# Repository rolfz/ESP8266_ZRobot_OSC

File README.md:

# ESP8266_ZRobot_OSC

EPS8266 based Robot with OSC based remote control. Robot can be controlled by iPhone or Smartphone, both config files are included.
The robot was based on FTobler Thingiverse 3d design http://www.thingiverse.com/thing:1230244

Functionality: The robot code was basically made to test the TOUCHOSC interface. OSC allows to communicate both 
	ways between ESP8266 and a smart-phone. All code runs on the ESP module (No Arduino Hardware required).
- "Speed" cursor will define the speed of the step motors advance.
- "Direction" cursor adds or deducts a value from the speed making the robot turn left-right
- "Reverse" button inverses the motor rotation = reverse the engine direction like a car.
- 3 buttons "Turn Left, Center, Turn right" are preprogrammed directions for the robot
- "RUN" button will start the engine and also stop everything if cancelled.
- One status line is used to send instructions to the pilot
- One distance message box will indicate the distance to the next object (to be implemented).
- Current time and Smartphone battery are shown on the display

### Basic ideas, origin of the project:

- ftobler 3d files printed on Lulzbot TAZ4 printer.
- two 28byj-48 stepper motors with driver circuit from ebay
- ESP8266 12E module
	
###Changes, additions:

- ESP was programmed with Arduino based environment and ESP plug-in
- Accelstepper library (http://www.airspayce.com/mikem/arduino/AccelStepper/).
- Tutorial can be found here: (https://www.pjrc.com/teensy/td_libs_AccelStepper.html).
- LV-MAXSonar-EZ0 from Sparkfun
- self made board to hold the ESP module, with 2 push buttons for reset and setting programming mode, 
  led and connectors for the peripherals.
- Alternative battery holder to hold a 2S Lipo
- Alternative motor connections to simplify the wiring on the self made board.

### TouchOSC:

I discovered this app by accident when I looked at B-Robot and similar projects. Some tests made with 
Blynk which looks even more attractive made visible the current advantage of OSC! Easy implementation,
easy to use windows application to create the GUI, easy to load on a second or alternative platform 
and sizable widgets which are not yet possible on Blynk made me keep OSC for this project. Maybe I 
missed something on Blynk, at least it was not immediately visible that the features I missed where 
available. TouchOSC design tool is available for free from http://hexler.net/software/touchosc, you 
will need to pay for the user interface you download on your phone or tablet.

My current TouchOSC design:

OSC config: 
----------
Simple-Z-Robot-Iphone5.touchosc
Simple-Z-Robot-Samsung.touchosc
	
Code:
----
ESP8266_ZRobot_OSC.ino includes all Zrobot specific code.

Schematic:
---------
[schematic.pdf](schematic.pdf) and eagle files

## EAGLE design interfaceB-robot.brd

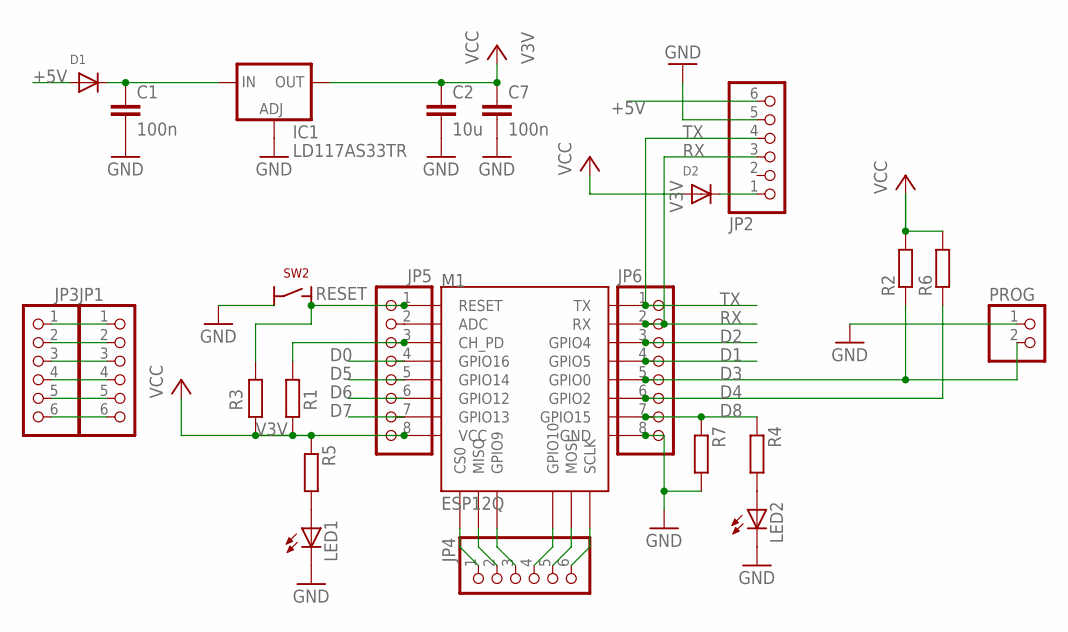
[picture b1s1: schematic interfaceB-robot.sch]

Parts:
C1: 100n; C1206K
C2: 10u; C1206K
C7: 100n; C0805
D1, D2: DIODE_SOD-123FL; SOD-123FL
IC1: LD117AS33TR; SOT223
JP1, JP2, JP3, JP4: PINHD-1X6; 1X06
JP5, JP6: PINHD-1X8; 1X08
LED1, LED2: LEDCHIPLED_0805; CHIPLED_0805
M1: ESP12Q
PROG: PINHD-1X2; 1X02
R1, R3: R-EU_R1206; R1206
R2, R4, R5, R6, R7: R-EU_R0805; R0805
SW2: SW4; SW45-65

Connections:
+5V: D1.A, JP2.6
D0: JP5.4, M1.GPIO16
D1: JP6.4, M1.GPIO5
D2: JP6.3, M1.GPIO4
D3: JP6.5, M1.GPIO0, PROG.2, R2.1
D4: JP6.6, M1.GPIO2, R6.1
D5: JP5.5, M1.GPIO14
D6: JP5.6, M1.GPIO12
D7: JP5.7, M1.GPIO13
D8: JP6.7, M1.GPIO15, R4.1, R7.1
GND: C1.2, C2.2, C7.2, IC1.1 (ADJ), JP2.5, JP6.8, LED1.C, LED2.C, M1.GND, PROG.1, R7.2, SW2.4
unnamed: C1.1, D1.C, IC1.3 (IN)
unnamed: JP5.2, M1.ADC
unnamed: JP1.1, JP3.1
unnamed: D2.C, JP2.1
unnamed: JP1.2, JP3.2
unnamed: JP1.3, JP3.3
unnamed: JP1.4, JP3.4
unnamed: JP1.5, JP3.5
unnamed: JP1.6, JP3.6
unnamed: LED1.A, R5.2
unnamed: LED2.A, R4.2
unnamed: JP4.1, M1.CS0
unnamed: JP4.2, M1.MISO
unnamed: JP4.3, M1.GPIO9
unnamed: JP4.4, M1.GPIO10
unnamed: JP4.5, M1.MOSI
unnamed: JP4.6, M1.SCLK
PD: JP5.3, M1.CH_PD, R1.1
RESET: JP5.1, M1.RESET, R3.1, SW2.2 (S)
RX: JP2.3, JP6.2, M1.RX
TX: JP2.4, JP6.1, M1.TX
V3V: C2.1, C7.1, D2.A, IC1.4 (OUT), JP5.8, M1.VCC, R1.2, R2.2, R3.2, R5.1, R6.2

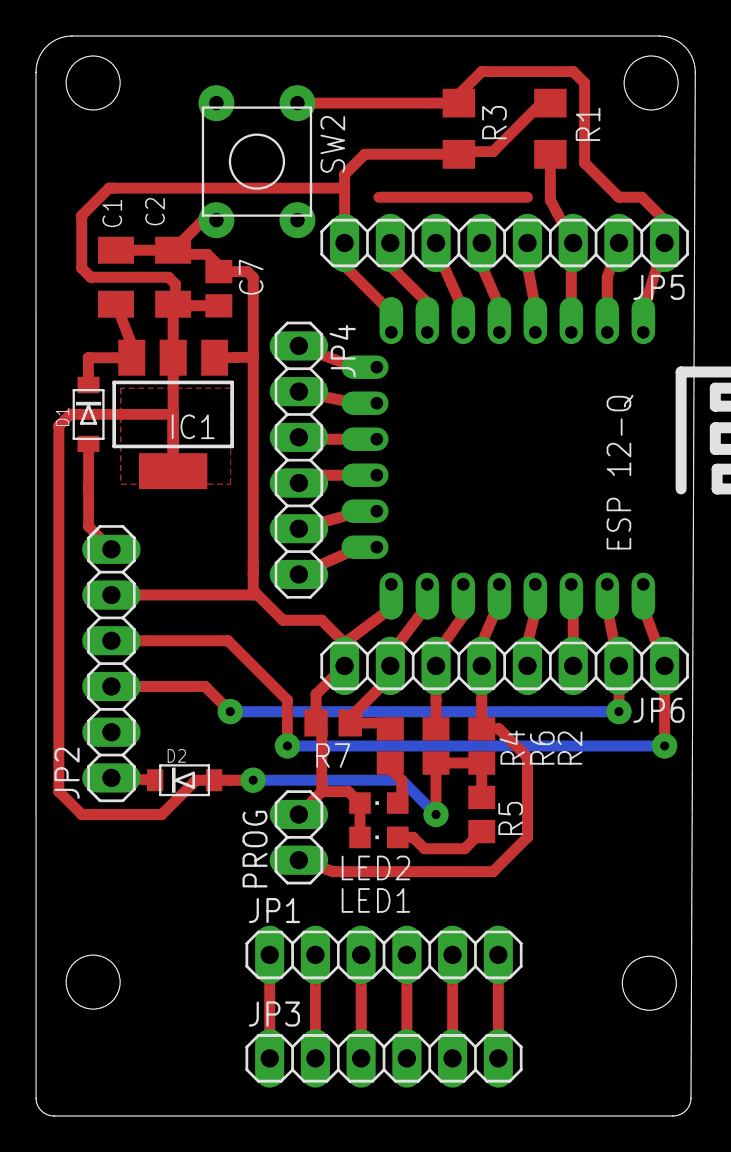
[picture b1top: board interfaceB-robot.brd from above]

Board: 2 copper layers, 36.6 x 60.0 mm, 24 parts (0 on the bottom side), 33 nets.

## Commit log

2016-04-24 first version
2016-04-24 TOUCHOSC files 1st version on GIT
2016-04-24 added picture tu readme
2016-04-24 new link
2016-04-24 new format
2016-04-24 added picture for OSC
2016-04-24 resized pic
2016-04-24 no message
2016-04-24 original PCB & Schematic
2016-04-24 added schematic
2016-04-24 reorganized files
2016-04-25 Corrections made to include the reverse gear, also the pin assignement for the step motors was not correct, wiring needs to be 1324 and not 1234 (setup in the code). Code may need a little adjustment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
2016-04-25 reverse mode did not work
2016-04-26 renamed command calls, working on ADC mesure of Ultrasonic module, not yet ready. ESP8266 seems to have a problem with ADC, also mesuring it in the main loop at the same speed reduced the speed and i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
2016-05-10 Added Soft-AP mode allowing robot to be used without router connection.
2016-05-10 Soft-AP version, some data sent back from OSC still do not update and need some more work. Robot control (ESP to mobile device) works fine.
2016-05-10 Added Stop button under Power Slider
2016-05-11 additional parts for 2 wheel robot, tyre printed with ninjaflex (print with scale x+y at 97%) and ultrasonic mounting front for LV-MaxSonar part
